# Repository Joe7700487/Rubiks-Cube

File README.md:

# Rubiks-Cube

This repository contains software and hardware work for a Rubik's Cube project: Python-based solvers and visualizers, a C++ solver prototype, firmware for a motorized mechanism, and KiCad PCB files.

## Repository layout

- `Python Solver/`
  - `cube.py`: 3x3 pygame-based cube visualizer and solver experiments. Based off this article https://observablehq.com/@onionhoney/how-to-model-a-rubiks-cube
  - `4x4solver.py`: 4x4 solver work using pruning tables and iterative deepening search.
  - `4x4visual.py`: helper script for converting or visualizing 4x4 facelet states.
  - `MoveConverter.py`: utility script that rewrites move sequences into the move vocabulary used by the robot.
  - `*PruningTable.py`, `g3SolvedStates.py`: precomputed search data and solved-state helpers used by the Python solvers.
- `C++ Cube Solver/`
  - Visual Studio solution for a C++/SDL3 cube renderer and move application prototype.
- `Firmware/`
  - `3motortest.ino`: ESP32/Arduino firmware for driving three steppers and servos to execute cube moves.
- `PCB/Driver/`
  - KiCad design files for the cube driver prototype board.
- `3D models/`
  - Reserved for CAD or printable mechanical parts.

## Python solver tools

The Python code is where most of the cube logic currently lives. It includes:

- Facelet-based move application.
- Geometric sticker representations for cube state conversion.
- Pruning-table-driven search for 3x3 and 4x4 solving stages.
- A move conversion helper for translating notation into the robot-friendly move set.

### Python requirements

Install Python 3.10+ and the runtime dependencies used by the scripts:

```powershell
pip install pygame numpy
```

### Running the Python scripts

From the repository root:

```powershell
cd "Python Solver"
python MoveConverter.py
python cube.py
python 4x4solver.py
python 4x4visual.py
```

Notes:

- `MoveConverter.py` is the simplest standalone utility and prints a converted move sequence.
- `cube.py`, `4x4solver.py`, and `4x4visual.py` open pygame windows and are set up as interactive experiment scripts rather than polished command-line tools.
- The pruning-table modules are committed directly in the repository, so there is no separate generation step required just to run the current Python code.

## C++ solver prototype

The `C++ Cube Solver` folder contains a Visual Studio solution targeting Windows and SDL3. The current code focuses on:

- Representing a 3x3 cube as a fixed-size array.
- Applying face turns efficiently.
- Rendering a cube net with SDL3.
- Basic keyboard-triggered test actions.

### C++ requirements

The Visual Studio project currently references SDL3 from a local path

### Building the C++ project

1. Open `C++ Cube Solver/Cube Solver.sln` in Visual Studio 2022.
2. Install or point the project at a local SDL3 checkout.
3. Select `Debug|x64` or `Release|x64`.
4. Build and run the `Cube Solver` project.

The current SDL application can render the cube net and respond to a few keyboard events for testing moves and performance.

## Firmware

`Firmware/3motortest.ino` is an Arduino-style control program for a three-motor cube turning mechanism. It uses:

- `AccelStepper`
- `Wire`
- `Adafruit_PWMServoDriver`

The firmware appears to target an ESP32-based setup with:

- Three stepper channels for face turns.
- A PCA9685 servo driver.
- Servo-controlled hands and a blocking mechanism.
- Serial move input such as `R`, `U`, `B`, wide moves, triple-layer moves, primes, and double turns.

### Firmware setup

1. Open `Firmware/3motortest.ino` in the Arduino IDE or PlatformIO.
2. Install the required libraries.
3. Select the correct ESP32 board and serial port.
4. Upload the sketch.
5. Send newline-terminated move commands over serial.

The special serial command `S` runs a built-in demonstration sequence.

## PCB files

The `PCB/Driver` directory contains the KiCad project for the driver board, including schematic, PCB layout, footprints, symbols, drill files, and Gerber job data.

Open `PCB/Driver/Driver.kicad_pro` in KiCad to inspect or modify the design.

## Project status

This repository is best understood as an actively developed project workspace rather than a packaged library. The main value is in the implementation details for cube state handling, solver experiments, and the integration path from software to physical hardware.

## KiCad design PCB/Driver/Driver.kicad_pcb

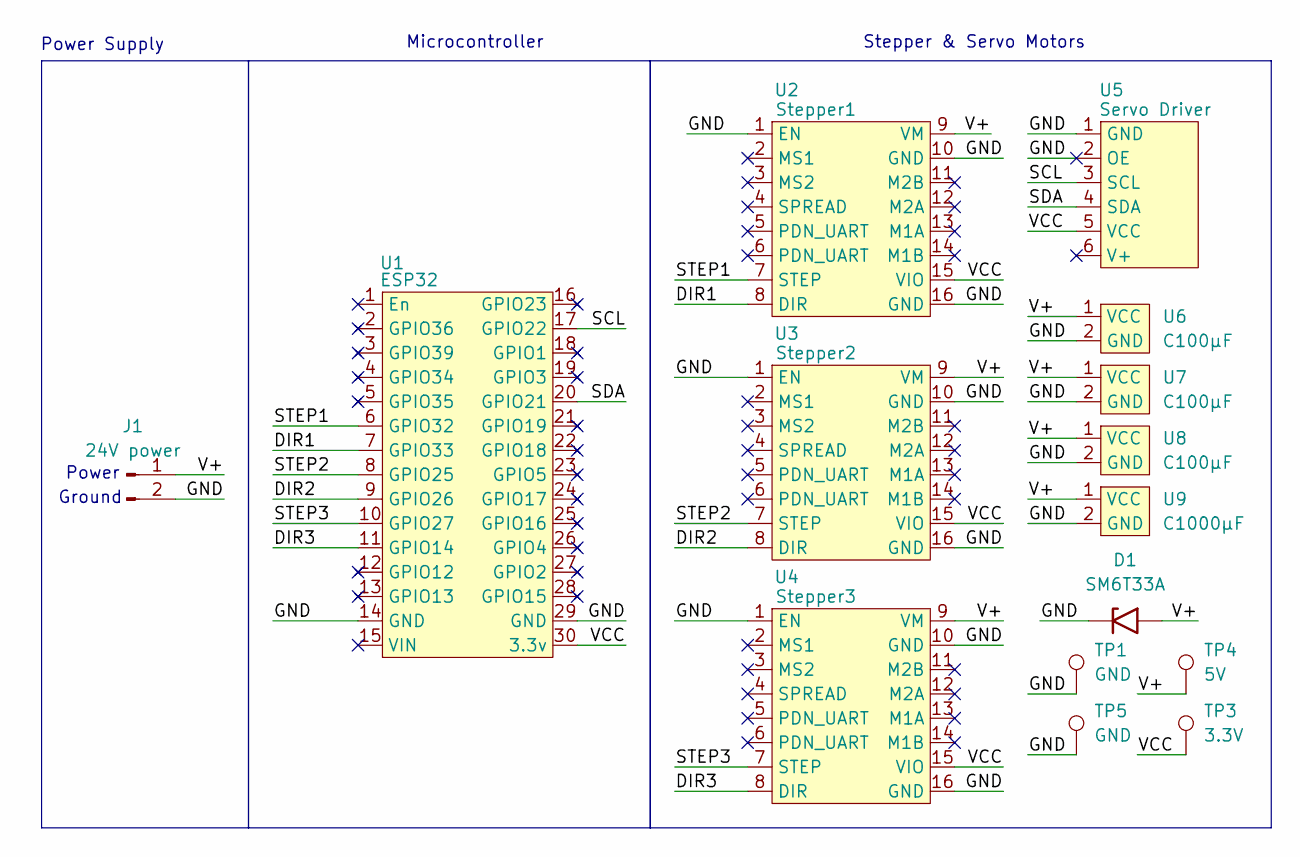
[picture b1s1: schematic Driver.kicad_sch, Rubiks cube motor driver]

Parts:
D1: SM6T33A; D_SMB
J1: 24V power; PinHeader_1x02_P2.54mm_Vertical
TP1, TP5: GND; TestPoint_Keystone_5000-5004_Miniature
TP3: 3.3V; TestPoint_Keystone_5000-5004_Miniature
TP4: 5V; TestPoint_Keystone_5000-5004_Miniature
U1: ESP32
U2: Stepper1; TMC2209
U3: Stepper2; TMC2209
U4: Stepper3; TMC2209
U5: Servo Driver; PCA9685
U6, U7, U8: C100µF; Capacitor
U9: C1000µF; Capacitor_1

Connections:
/DIR1: U1.7 (GPIO33), U2.8 (DIR)
/DIR2: U1.9 (GPIO26), U3.8 (DIR)
/DIR3: U1.11 (GPIO14), U4.8 (DIR)
/GND: D1.1 (A1), J1.2, TP1.1, TP5.1, U1.14 (GND), U1.29 (GND), U2.1 (EN), U2.10 (GND), U2.16 (GND), U3.1 (EN), U3.10 (GND), U3.16 (GND), U4.1 (EN), U4.10 (GND), U4.16 (GND), U5.1 (GND), U5.2 (OE), U6.2 (GND), U7.2 (GND), U8.2 (GND), U9.2 (GND)
/SCL: U1.17 (GPIO22), U5.3 (SCL)
/SDA: U1.20 (GPIO21), U5.4 (SDA)
/STEP1: U1.6 (GPIO32), U2.7 (STEP)
/STEP2: U1.8 (GPIO25), U3.7 (STEP)
/STEP3: U1.10 (GPIO27), U4.7 (STEP)
/V+: D1.2 (A2), J1.1, TP4.1, U2.9 (VM), U3.9 (VM), U4.9 (VM), U6.1 (VCC), U7.1 (VCC), U8.1 (VCC), U9.1 (VCC)
/VCC: TP3.1, U1.30 (3.3v), U2.15 (VIO), U3.15 (VIO), U4.15 (VIO), U5.5 (VCC)

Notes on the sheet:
Microcontroller
Stepper & Servo Motors
Ground
Power
Power Supply

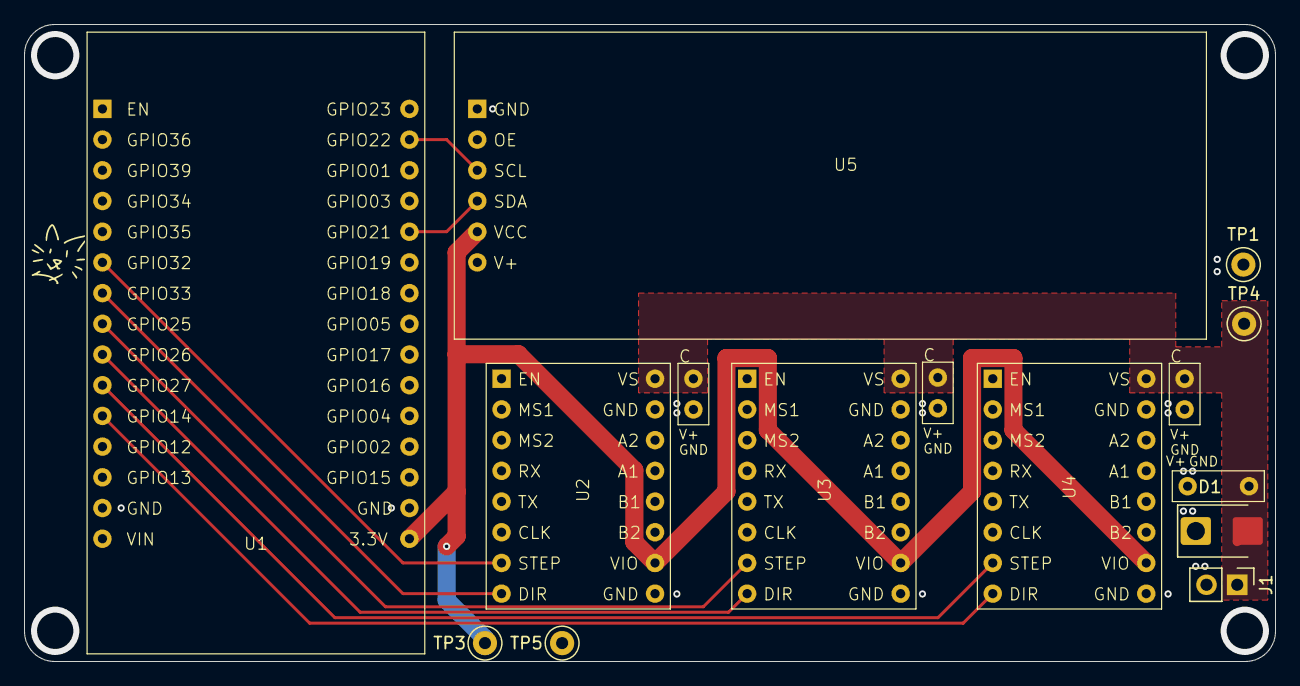
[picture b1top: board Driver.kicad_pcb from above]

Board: 2 copper layers, 103.5 x 52.7 mm, 15 parts (0 on the bottom side), 11 nets.

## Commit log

2025-10-23 Init commit
2025-10-24 Draw state
    added function to draw a cubes state
2025-10-24 created U move
    added a function that applies a U move to the cube state
2025-10-24 Added all standard moves
    added functions to move each face in both directions and a function to apply algorithms
2025-11-03 improved facelet visualization
2025-11-03 begin implementing geometric model
2025-11-04 Added geometric model for permutation
2025-11-05 generated facelet moves using new move conversion function
2025-11-05 added basic dfs and iddfs solvers
2025-11-07 Cleaned up python project and optimized fmoves
2025-11-07 added pruning table generator with solver
2025-11-08 created g1 solver with pruning table
2025-11-10 Functioning 3x3 solver
2025-11-10 Cleaned code slightly
2025-11-11 begin c++ code
2025-11-12 4x4 gcube model implemented in python
2025-11-12 generated 4x4 f moves
2025-11-14 4x4 first two center solver
2025-11-17 centers are made opposite
2026-01-07 vibe coded solution converter
2026-01-07 Created arduino code to drive motors and servos
2026-01-08 functional tperm demo
2026-01-09 fixed move conversion script
2026-01-10 4x4 facelit visualizer
2026-02-01 Function to solve test solution
2026-02-03 Migrate to esp32
2026-03-16 Add proto pcb and organize codebase
2026-03-16 add 3d models
2026-05-20 models
